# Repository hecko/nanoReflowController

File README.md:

Reflow Oven Controller
====================

**News**

* Forked from 0xPIT & uploaded the code after a lot of restructuration
* Board design has also changed

**Arduino-based reflow oven controller with:**
* [PID] loop control
* [Wave Packet] control for AC output
* graphic TFT LC-Display, drawing the temperature curves
  * using a 5v compatible 1.8" of 1.44" TFT SPI display with ST7735 controller
* solely controlled using a cheap rotary encoder and its single button
* uses a MAX6675 module as interface to a K type thermocouple
* stores up to 30 temperature profiles in EEPROM
* configurable PID-parameters
* simple, small hardware to drive loads up to 600V and up to 2A without heatsink
* powered throuhg one of three options: 12v RAW pin, 5v pin or 5v USB
* optional 12v fan control (not yet implemented in the code)
* *Please Note*: Requires Arduino IDE 1.5.x or newer

(c) 2017 David Sanz Kirbis
(c) 2014 Karl Pitrich <karl@pitrich.com>
in part based on a project (c) 2013 Ed Simmons <ed@estechnical.co.uk>

## Warning: This project operates with possibly lethal mains voltage. If you are unsure what to do, don't do it and get help from an experienced tinkerer with professional training.

**Minimal build**

![BoardPic1] | ![BoardPic2]
------------ | -------------

**Completely populated**

![Complete1] | ![Complete2] | ![Complete3]
------------ | ------------ | -------------

**Enclosed and mounted on halogen floodlight**

(more info: [Halogen Floodlight SMT reflow])

![Floodlight]
--------------

<!---
**Post action shot**

![CycleWithOverflow] | ![Warning]
------------ | -------------

Introduction
====================

This Reflow Oven Controller relies on an [Arduino Nano] easily obtainable on eb*y for less than $10, plus my custom shield, which is actually more like a motherboard.

As I believe it is not wise to have a mess of wiring and tiny breakout-boards for operating mains powered equipment, I've decided to design custom board with easily obtainable components.

The hardware can be found in the [folder hardware], including the Eagle schematics and PCB layout files. It should fit the freemium version of Eagle. Here are preview images:

![PCB][ImgPCB]
![Schematic][ImgSCH]

The board contains the [Arduino Nano], very simple [Zero crossing] detection circuit, used to align control logic to mains frequency, two [MAX31855] thermocouple-to-digital converters and two [Sharp S202S01] PCB-mount solid state relays, mounted on cheap [Fischer SK409 50,8] heat sinks. The current software uses only one of the thermocouples, so you need to populate one IC only. If you're lucky, you can get free samples of the MAX31855 from Maxim.

The software uses [PID] control of the heater and fan output for improved temperature stability. The heater AC load is controlled using [Wave Packet] control in order to minimize RF interference and load on the relay. For the fan motor, [Phase Fired] control has been implemented.

Please note that all important timings are *based on the mains frequency*, so the circuit will **not work** properly without mains connection.

But for testing, I've added an additional timer to simulate the zero-crossings, in order to run the software without being connected to mains. The software should work in 50 and 60Hz mains, the 60Hz version is not tested, though.

Errata and construction infos
========

Issue | Notes
------------ | -------------

Screenshots and usage information
========

Image | Information
------------ | -------------
![CycleWithOverflow] | *Display after a cylcle has been completed. The blue line is the setpoint, the red line the actual temperature measured by the thermocouple. Note that the graph wraps around automatically. 'Sp' is the current setpoint calculated by the PID loop. In the lower line there are: Current heater and fan outputs, both in percent, and the current temperature rise or drop rate in °C per second. The graph will draw orientation lines every 50°C up to the peak temperature set in the selected profile.*
![MenuDefault] | *The main menu can be navigated by rotating the encoder (sic!). Clicking enters the menu item, or navigates to the submenu. Doubleclick moves up or back or exits the menu item.*
![FanSpeedEdit] | *To edit a setting, click once to enter edit mode (red cursor), then rotate to change the value, click again to save. Doubleclick will exit without saving.*
![MenuEditProfile] | -
![ProfileSettings] | *Typical solder profile settings...*
![ProfileSettingsEdit] | *These parameters can be easily edited using the encoder as described above.*
![MenuLoadProfile] | *Up to 30 Profiles can be loaded and saved. You have to do this manually, so that you can have 'save-as' functionality without overwriting existing profiles.*
![PIDValues] | *Current pid values for my 1300W 20$ toaster oven.*
![PIDValuesEdit] | *Editing is simple, like above. Note that, unlike with the profile settings, the PID values will be automatically stored to EEPROM when you exit the submenu by doubleclicking.*
--->

Obtaining the source code
====================

Get the code using `git`.

	git clone https://github.com/hecko/nanoReflowController.git

or [download a Snapshot].

I've added some libraries I've used as submodules to the git repositroy, so it is important that, after cloning this repository, you do 

    git submodule update --init

to fetch all involved libraries. (See: [Submodule Cheat Sheet])

Installation
====================

Of course, you need to have the Arduino IDE installed. I've worked with version 1.5.x only and I will not support older versions. Get it from the [Arduino Download] page or upgrade you current Arduino setup.

There as several dependencies you need to install. 

If you are unfamiliar with Arduino Libraries, please read [the library guide].
Basically, each library needs to be liked or copied into your Arduino library folder.

<!---
My code uses [TimerOne] for basic timing, for the 1.8" TFT I've used [Adafruit_ST7735], which requires [Adafruit_GFX]. I **strongly suggest** to use my **modified version** of [Adafruit_ST7735-pit], as it **performs much better**, but requires you to use SPI, which my board does anyway.

For the user interface you require my own [Menu] and [ClickEncoder] libraries, which are included as submodules.

All other libraries need to be downloaded and installed.

After you've installed all libraries, open the Arduino IDE, open the ReflowController.pde sketch (using File->Open).

Select the right hardware from the Tools->Board menu.

Compile the firmware (Sketch->Verify) to test everything is installed correctly. If something's wrong, feel free to post an issue here on github, I will look into it.

Now, choose the correct serial port from Tools->Serial Port and then upload the code.
*Remember* that a standard compile will get stuck at "Calibrating..." without proper mains connection, so that zero crossing interrupts can occur.

I could not fit PID Autotuning into the limited space of the Arduino in addition the normal code. So if you want to try to autotune you PID Loop, install the [PID_AutoTune] Library, `#define PIDTUNE 1` in the .ino file, then recompile and download do the Arduino.

As all timing relies on Zero Crossing detection, you need to `#define FAKE_HW 1` and install [TimerThree] when you want to run without actual hardware *and/or* without mains connection.

Things to note
====================

* The [MAX31855] does not like the thermocouple being grounded; It must be isolated from ground or earth.
* The PID Loop must be tuned individually for each oven. It will *not* work out of the box. 
* [PID Autotune] is not very useful, as it seems to be able to tune only to keep a specific temperature value, which is not what we do in a reflow oven. Also, at least my oven seems to be very non-linear when heating up.
* When rewiring inside your oven, use only wiring that can withstand high temperatures. I use silicone coated lace.
* Do not solder wiring inside you oven, the temperature might desolder you joints. **Crimp everything.**
* Use proper earth ground connection for your ovens chassis.

Ideas and todo
====================
* Optimize code size so that more features can fit
* Clamp values for parameters to reasonalbe ranges
* Add scrollbar (sample implementation in the demo for [Menu]
* Separate PID configuration for each process step
* try to make the display faster, it is very slow
* Named profiles
* Rewrite [Menu] so that is uses callback objects instead of spaghetti-callbacks
--->

Licensing
====================
```
The MIT License (MIT)

Copyright (c) 2017 David Sanz Kirbis
All rights reserved.

Permission is hereby granted, free of charge, to any person obtaining a copy
of this software and associated documentation files (the "Software"), to deal
in the Software without restriction, including without limitation the rights
to use, copy, modify, merge, publish, distribute, sublicense, and/or sell
copies of the Software, and to permit persons to whom the Software is
furnished to do so, subject to the following conditions:

The above copyright notice and this permission notice shall be included in
all copies or substantial portions of the Software.

THE SOFTWARE IS PROVIDED "AS IS", WITHOUT WARRANTY OF ANY KIND, EXPRESS OR
IMPLIED, INCLUDING BUT NOT LIMITED TO THE WARRANTIES OF MERCHANTABILITY,
FITNESS FOR A PARTICULAR PURPOSE AND NONINFRINGEMENT. IN NO EVENT SHALL THE
AUTHORS OR COPYRIGHT HOLDERS BE LIABLE FOR ANY CLAIM, DAMAGES OR OTHER
LIABILITY, WHETHER IN AN ACTION OF CONTRACT, TORT OR OTHERWISE, ARISING FROM,
OUT OF OR IN CONNECTION WITH THE SOFTWARE OR THE USE OR OTHER DEALINGS IN
THE SOFTWARE.
```

[PID Autotune]:https://github.com/br3ttb/Arduino-PID-AutoTune-Library
[Submodule Cheat Sheet]:http://blog.jacius.info/git-submodule-cheat-sheet/
[ESTechnical]:http://www.estechnical.co.uk
[Arduino Download]:http://arduino.cc/en/Main/Software
[folder hardware]:https://github.com/dasaki/nanoReflowController/tree/master/hardware
[download a Snapshot]:https://github.com/dasaki/nanoReflowController/archive/master.zip
[the library guide]:http://arduino.cc/en/Guide/Libraries
[PID]:http://en.wikipedia.org/wiki/PID_controller
[Wave Packet]:http://de.wikipedia.org/wiki/Schwingungspaketsteuerung
[Phase Fired]:http://en.wikipedia.org/wiki/Phase-fired_controllers 
[Adafruit 1.8" TFT]:http://www.adafruit.com/products/358
[MAX31855]:http://www.maximintegrated.com/en/products/analog/sensors-and-sensor-interface/MAX31855.html
[Fischer SK409 50,8]:http://www.pollin.de/shop/dt/NzE5OTY1OTk-
[Sharp S202S01]:http://sharp-world.com/products/device/lineup/data/pdf/datasheet/s102s01_e.pdf
[Zero crossing]:http://en.wikipedia.org/wiki/Zero_crossing
[TimerOne]:http://playground.arduino.cc/Code/Timer1
[TimerThree]:http://playground.arduino.cc/Code/Timer1
[Adafruit_ST7735]:https://github.com/adafruit/Adafruit-ST7735-Library
[Adafruit_GFX]:https://github.com/adafruit/Adafruit-GFX-Library
[Adafruit_ST7735-pit]:https://github.com/0xPIT/Adafruit-ST7735-Library
[Menu]:https://github.com/0xPIT/menu
[ClickEncoder]:https://github.com/0xPIT/encoder
[Arduino Nano]:https://store.arduino.cc/arduino-nano

[CycleWithOverflow]:https://raw.githubusercontent.com/0xPIT/reflowOvenController/master/images/CycleWithOverflow.jpg
[FanSpeedEdit]:https://raw.githubusercontent.com/0xPIT/reflowOvenController/master/images/FanSpeedEdit.jpg
[MenuDefault]:https://raw.githubusercontent.com/0xPIT/reflowOvenController/master/images/Menu.jpg
[MenuLoadProfile]:https://raw.githubusercontent.com/0xPIT/reflowOvenController/master/images/MenuLoadProfile.jpg
[MenuEditProfile]:https://raw.githubusercontent.com/0xPIT/reflowOvenController/master/images/MenuEditProfile.jpg
[PIDValuesEdit]:https://raw.githubusercontent.com/0xPIT/reflowOvenController/master/images/PIDValuesEdit.jpg
[ProfileSettings]:https://raw.githubusercontent.com/0xPIT/reflowOvenController/master/images/ProfileSettings.jpg
[PIDValues]:https://raw.githubusercontent.com/0xPIT/reflowOvenController/master/images/PIDValues.jpg
[ProfileSettingsEdit]:https://raw.githubusercontent.com/0xPIT/reflowOvenController/master/images/ProfileSettingsEdit.jpg

[Warning]:http://www.proshieldsafetysigns.co.uk/signs/59793_signs.jpg
[ImgPCB]:https://raw.githubusercontent.com/0xPIT/reflowOvenController/master/hardware/v0.2.brd.preview.png
[ImgSCH]:https://raw.githubusercontent.com/0xPIT/reflowOvenController/master/hardware/v0.2.sch.preview.png

[ImgMissingTrace]:https://raw.githubusercontent.com/0xPIT/reflowOvenController/master/images/MissingTrace.jpg
[BoardPic1]:https://raw.githubusercontent.com/dasaki/nanoReflowController/master/images/v1_0_Board_picture_top.jpg
[BoardPic2]:https://raw.githubusercontent.com/dasaki/nanoReflowController/master/images/v1_0_Board_picture_bottom.jpg
[Complete1]:https://raw.githubusercontent.com/dasaki/nanoReflowController/master/images/v1_0_Board_3d_01.png
[Complete2]:https://raw.githubusercontent.com/dasaki/nanoReflowController/master/images/v1_0_Board_3d_02.png
[Complete3]:https://raw.githubusercontent.com/dasaki/nanoReflowController/master/images/v1_0_Board_3d_03.png
[Floodlight]:https://raw.githubusercontent.com/dasaki/nanoReflowController/master/images/v1_0_floodlight_reflow.jpg
[Halogen Floodlight SMT reflow]:http://therandomlab.blogspot.com.es/2017/07/halogen-floodlight-smt-reflow.html

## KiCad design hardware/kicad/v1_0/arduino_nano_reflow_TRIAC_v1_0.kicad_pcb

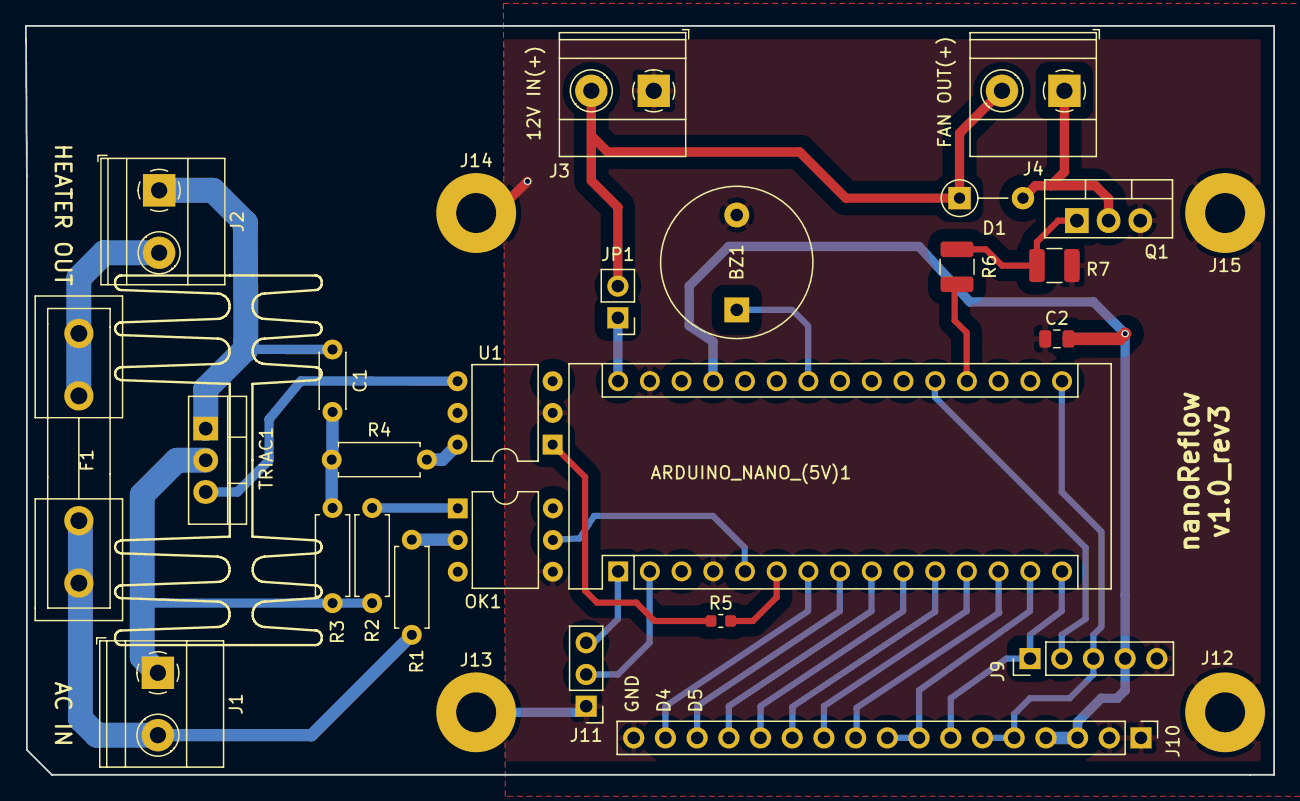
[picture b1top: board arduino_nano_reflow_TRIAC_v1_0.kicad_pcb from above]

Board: 2 copper layers, 100.0 x 60.0 mm, 30 parts (0 on the bottom side), 33 nets.

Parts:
ARDUINO_NANO_(5V)1: arduino_nano_header; Arduino_Nano
BZ1: Buzzer with generator; Buzzer_12x9.5RM7.6
C1: 10n; C_Disc_D4.3mm_W1.9mm_P5.00mm
C2: 100n; C_0805_2012Metric
D1: 1N4007; D_A-405_P5.08mm_Vertical_AnodeUp
F1: Fuse; Fuseholder5x20_horiz_open_inline_Type-I
J1: AC IN 220v; TerminalBlock_Phoenix_MKDS-1,5-2_1x02_P5.00mm_Horizontal
J2: HEATER; TerminalBlock_Phoenix_MKDS-1,5-2_1x02_P5.00mm_Horizontal
J3: DC IN 12V; TerminalBlock_Phoenix_MKDS-1,5-2_1x02_P5.00mm_Horizontal
J4: 12V FAN; TerminalBlock_Phoenix_MKDS-1,5-2_1x02_P5.00mm_Horizontal
J9: CONN_01X05; PinHeader_1x05_P2.54mm_Vertical
J10: CONN_01X17; PinHeader_1x17_P2.54mm_Vertical
J11: CONN_01X03; Pin_Header_Straight_1x03_Pitch2.54mm
J12, J13, J14, J15: MOUNTING_HOLE; MountingHole_3.2mm_M3_Pad
JP1: VIN enabler; Pin_Header_Straight_1x02_Pitch2.54mm
KK1: TRIAC HEATSINK; TO_220_heatsink
OK1: H11AA1; DIP-6_W7.62mm
Q1: IRF540N; TO-220-3_Vertical
R1, R2: 47k 0.6w; R_Axial_DIN0207_L6.3mm_D2.5mm_P7.62mm_Horizontal
R3: 2.4k; R_Axial_DIN0207_L6.3mm_D2.5mm_P7.62mm_Horizontal
R4: 180R; R_Axial_DIN0207_L6.3mm_D2.5mm_P7.62mm_Horizontal
R5: 1k; R_0603_1608Metric
R6: 4K7; R_1210_3225Metric
R7: 100K; R_1210_3225Metric
TRIAC1: BT137; TO-220-3_Vertical
U1: MOC3020M; DIP-6_W7.62mm

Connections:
5V: ARDUINO_NANO_(5V)1.27, C2.2, J9.4, J10.3, J10.4
12v: D1.1, J3.2, J4.2, JP1.2
/AC_CAP: C1.2, R3.1, R4.1
/BUZZER: ARDUINO_NANO_(5V)1.24, BZ1.1
/D4: ARDUINO_NANO_(5V)1.7, J10.16
/D5: ARDUINO_NANO_(5V)1.8, J10.15
/D6: ARDUINO_NANO_(5V)1.9, J10.14
/DIMM_CTRL: ARDUINO_NANO_(5V)1.6, R5.2
/FAN_CTRL: ARDUINO_NANO_(5V)1.19, R6.1
/FAN_GND: D1.2, J4.1, Q1.2
/LCD_CS: ARDUINO_NANO_(5V)1.13, J10.10
/LCD_DC: ARDUINO_NANO_(5V)1.12, J10.11
/LCD_RESET: ARDUINO_NANO_(5V)1.11, J10.12
/MISO: ARDUINO_NANO_(5V)1.15, J9.1, J10.7
/MOC_AC1: R4.2, U1.6
/MOC_AC2: TRIAC1.3, U1.4
/MOSI: ARDUINO_NANO_(5V)1.14, J10.8, J10.9
/OC1: OK1.1, R2.2
/OC2: OK1.2, R1.2
/SCK: ARDUINO_NANO_(5V)1.16, J9.3, J10.5, J10.6
/SD_CS: ARDUINO_NANO_(5V)1.10, J10.13
/TC_CS: ARDUINO_NANO_(5V)1.20, J9.2
/VIN: ARDUINO_NANO_(5V)1.30, JP1.1
/ZEROX: ARDUINO_NANO_(5V)1.5, OK1.5
AC1_IN: J1.1, R2.1, R3.2, TRIAC1.2
AC1_OUT: C1.1, J2.1, TRIAC1.1
AC2_IN: F1.2, J1.2, R1.1
AC2_OUT: F1.1, J2.2
GND: ARDUINO_NANO_(5V)1.4, ARDUINO_NANO_(5V)1.29, BZ1.2, C2.1, J3.1, J9.5, J10.1, J10.2, J10.17, J11.1, J12.1, J13.1, J14.1, J15.1, OK1.4, Q1.3, R7.1, U1.2
unnamed: ARDUINO_NANO_(5V)1.1, J11.3
unnamed: ARDUINO_NANO_(5V)1.2, J11.2
unnamed: Q1.1, R6.2, R7.2
unnamed: R5.1, U1.1

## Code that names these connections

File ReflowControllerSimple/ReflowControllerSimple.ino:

//
// This version does not use display, buttons or other fancy stuff and only
// works as a very fundamental baker - reach TARGET_TEMP, tne turn FAN on and
// then end forever until reset
//

#include "max6675.h"
#include <TM1637Display.h>

#define PIN_HEATER 3

#define PIN_LCD_VCC 4
#define PIN_LCD_DIO 5
#define PIN_LCD_CLK 6

#define PIN_LCD_CS 10

#define PIN_TC_CS A1
#define PIN_TC_DO 12
#define PIN_TC_CLK 13
#define FAN_PIN A0
#define BUZZER_PIN A5

#define TARGET_TEMP 250

TM1637Display display(PIN_LCD_CLK, PIN_LCD_DIO);
MAX6675 thermocouple(PIN_TC_CLK, PIN_TC_CS, PIN_TC_DO);

void setup() {
  pinMode(PIN_HEATER, OUTPUT);
  pinMode(FAN_PIN, OUTPUT);
  pinMode(BUZZER_PIN, OUTPUT);
  pinMode(PIN_LCD_VCC, OUTPUT);
  digitalWrite(PIN_LCD_VCC, HIGH);

  display.setBrightness(0x0f);
  display.showNumberDec(8888, false);

  tone(BUZZER_PIN, 4000);
  delay(100);
  noTone(BUZZER_PIN);

  digitalWrite(PIN_HEATER, 0);

  Serial.begin(115200);
  Serial.println("begin");
}

float t = 100;

void loop() {
  t = readThermocouple();
  t = readThermocouple();
  if ((t > 260) || (t <= 0)) {
    Serial.println("Kill heater - something wrong with temperature probe!");
    Serial.print("current C: ");
    Serial.println(round(t));
    digitalWrite(PIN_HEATER, LOW);
    while (1) {
      tone(BUZZER_PIN, 4000);
      delay(2000);
      noTone(BUZZER_PIN);
      delay(1000);
    };
  }

  Serial.print("target C: ");
  Serial.print(TARGET_TEMP);
  Serial.print(" -> ");
  Serial.print("current C: ");
  Serial.print(round(t));
  Serial.print(" -> ");
  display.clear();
  delay(50);
  display.showNumberDec(t, false);

  if (t < TARGET_TEMP) {
    Serial.println("ON!");
    digitalWrite(PIN_HEATER, HIGH);
  } else {
    Serial.println("Temperature reached - turning OFF forever!");
    fan_on();
    digitalWrite(PIN_HEATER, LOW);
    while (1) {
      Serial.println("Temperature reached - turning OFF forever!");
      t = readThermocouple();
      Serial.print("Current C: ");
      Serial.println(round(t));
      display.clear();
      delay(50);
      display.showNumberDec(t, false);
      if (t < 150 && t >= 45) {
        // part can be taken from the heating lamp
        tone(BUZZER_PIN, 6000);
        delay(50);
        noTone(BUZZER_PIN);
        delay(5000);
      }
      if (t < 45) {
        fan_off();
        tone(BUZZER_PIN, 4000);
        delay(1000);
        noTone(BUZZER_PIN);
        delay(15000);
      }
    }
  }
}

void fan_on() {
  Serial.println("Turning FAN ON!");
  analogWrite(FAN_PIN, 255);
}

void fan_off() {
  Serial.println("Turning FAN OFF!");
  analogWrite(FAN_PIN, 0);
}

float readThermocouple() {
  digitalWrite(PIN_TC_CS, LOW);
  delay(100); // otherwise does not work!!
  float temperature = thermocouple.readCelsius();
  delay(1000); // otherwise does not work!!

  if (temperature == NAN) {
    Serial.println("Unable to read temperature!");
    temperature = -100;
  }

  digitalWrite(PIN_TC_CS, HIGH);
  return temperature;
}

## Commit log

2017-11-13 added part list and sources for pelectronic parts
2017-11-14 mode parts from farnell
2017-11-14 added gerbers that have been sent to elecrow
2017-11-14 updated bom-sk
2017-11-14 clarification BOM
2017-11-14 fix link
2017-11-14 install script
2017-12-03 pridana objednana poistka
2017-12-03 added r1, r2 resistors farnell reference
2017-12-03 headed update to prettify
2019-12-29 unpack kicad files
2019-12-29 upgrade to kicad 5.1.5
2020-05-22 update installation script
2020-05-22 - new revision of board - suitable for production with oshpark - updated footprints - cross checked with original schematics
2020-05-22 added fundamentally trivial script to test the heater - just keeps resired tenperature forever, no profiles, nothing
2020-05-22 update footprint to match kicad 5.1.6 - SIP suitable for oshpark
2020-05-25 clean up the code
2020-05-25 pid as module
2020-09-16 update code
2020-09-16 add buzzer
2020-09-16 beep better
2020-09-16 add beeping when temperature <150
2020-09-17 add cad files for 3d printing
2020-09-17 updated PCB to v1.0_rev3 - more space for connectors and rewired for better access to FAN port
2020-09-17 remove gerbers zip file
2020-09-17 add missing heatsink footprint
2021-01-08 update - make sure to not turn anything on when temperature == 0
2021-01-21 update - poslane do vyroby
2021-01-21 add simple and cheap TM1637 display to simple firmware
2021-02-19 add firmware for new pcb
2021-03-03 change dir
2021-12-15 update cad
2022-01-12 firmware pre kalibracny kupel
2022-01-17 presun ac suciastok tak aby bolo viac miesta + zmena footprintov pre vykonove suciastky
